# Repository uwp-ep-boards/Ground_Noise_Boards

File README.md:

# Ground_Noise_Boards
Circuit boards to support Ground Noise in Digital Logic lab.

Boards designed by Johnathan Trachte for labs by Dr. Hal Evensen, under guidance by Dr. Cyrus Habibi.

## Revision History
### Signal Board
0.0.2 \
    - Remove grounding from digital logic outputs \
    - Fix LM317LZ silkscreen orientation \
    - Swap LM317LZ programming resistor values to allow minimum current draw under no load \
    - Modify resistor footprint for horizontal mounting \
    - Adjust various power routing as pours instead of tracks \
    - Add test points for critical signals \

### Return Board
0.0.2 \
    - Remove grounding from digital logic outputs \
    - Fix LM317LZ silkscreen orientation \
    - Swap LM317LZ programming resistor values to allow minimum current draw under no load \
    - Modify resistor footprint for horizontal mounting \
    - Add test points for critical signals \

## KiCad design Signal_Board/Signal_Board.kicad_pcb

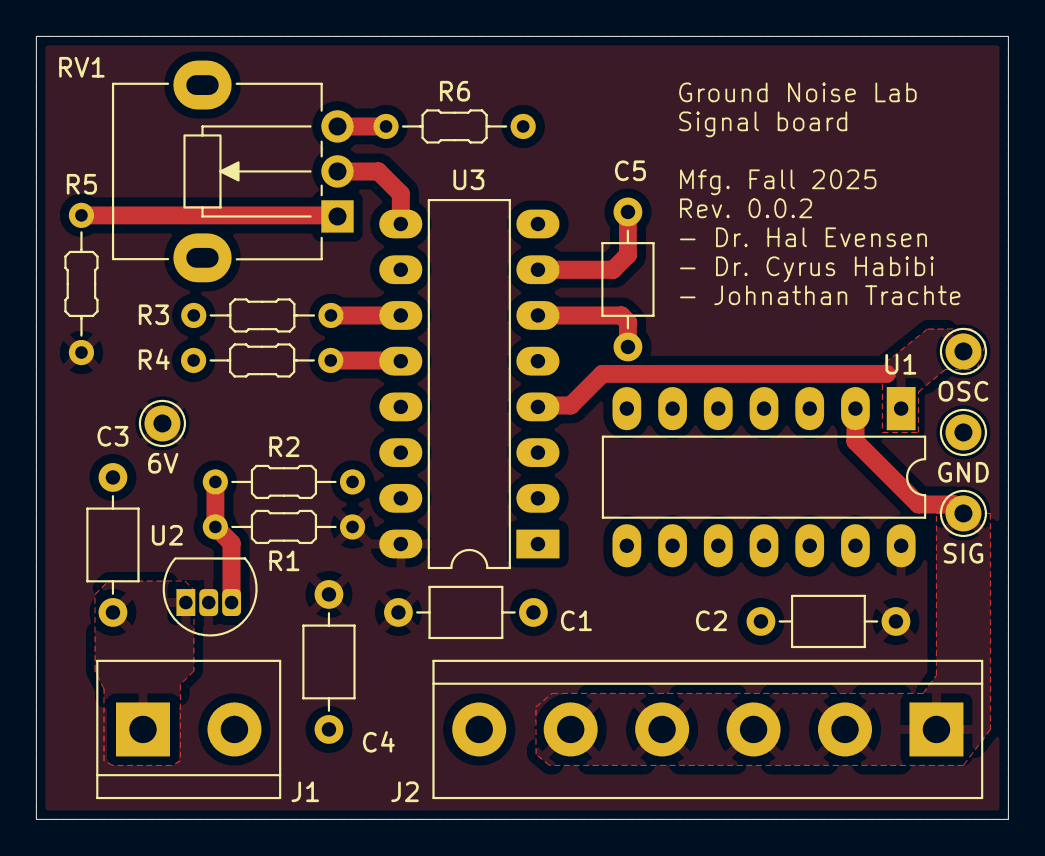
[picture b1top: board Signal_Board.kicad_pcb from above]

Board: 2 copper layers, 54.0 x 43.5 mm, 21 parts (0 on the bottom side), 13 nets.

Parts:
6V: 6 V; Pin_D1.0mm_L10.0mm
C1, C2, C3: 0.1u; C_Axial_L3.8mm_D2.6mm_P7.50mm_Horizontal
C4: 1u; C_Axial_L3.8mm_D2.6mm_P7.50mm_Horizontal
C5: 47p; C_Axial_L3.8mm_D2.6mm_P7.50mm_Horizontal
GND: GND; Pin_D1.0mm_L10.0mm
J1: Conn_01x02_Pin; TerminalBlock_bornier-2_P5.08mm
J2: Conn_01x06_Pin; TerminalBlock_bornier-6_P5.08mm
OSC: Osc; Pin_D1.0mm_L10.0mm
R1: 240; R_Axial_DIN0204_L3.6mm_D1.6mm_P7.62mm_Horizontal
R2: 910; R_Axial_DIN0204_L3.6mm_D1.6mm_P7.62mm_Horizontal
R3: 1k13; R_Axial_DIN0204_L3.6mm_D1.6mm_P7.62mm_Horizontal
R4: 31k6; R_Axial_DIN0204_L3.6mm_D1.6mm_P7.62mm_Horizontal
R5: 1k; R_Axial_DIN0204_L3.6mm_D1.6mm_P7.62mm_Horizontal
R6: 0; R_Axial_DIN0204_L3.6mm_D1.6mm_P7.62mm_Horizontal
RV1: 1M; Potentiometer_Alpha_RD901F-40-00D_Single_Vertical
SIG: Sig; Pin_D1.0mm_L10.0mm
U1: 74HC14; DIP-14_W7.62mm_LongPads
U2: LM317LZ; TO-92L_Inline
U3: 4046; DIP-16_W7.62mm_LongPads

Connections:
+6V: 6V.1, C1.1, C2.1, C4.1, R1.1, R5.1, U1.14 (VCC), U2.3 (OUT), U3.16 (VDD)
+9V: C3.1, J1.1, U2.2 (IN)
/CAP_FB: C5.1, U3.7 (C2)
/LDO_ADJ: R1.2, R2.1, U2.1
/R1: R3.1, U3.11 (R1)
/R2: R4.1, U3.12 (R2)
/SIG_Out: J2.1, J2.2, J2.3, J2.4, J2.5, SIG.1, U1.2
/VCO_IN: RV1.2, U3.9 (VCOin)
GND: C1.2, C2.2, C3.2, C4.2, GND.1, J1.2, J2.6, R2.2, R3.2, R4.2, R6.2, U1.3, U1.5, U1.7 (GND), U1.9, U1.11, U1.13, U3.5 (Inh), U3.8 (VSS), U3.10 (SFout), U3.15 (ZOUT)
unnamed: R5.2, RV1.1
unnamed: R6.1, RV1.3
unnamed: C5.2, U3.6 (C1)
OSC_Out: OSC.1, U1.1, U3.4 (FOUT)

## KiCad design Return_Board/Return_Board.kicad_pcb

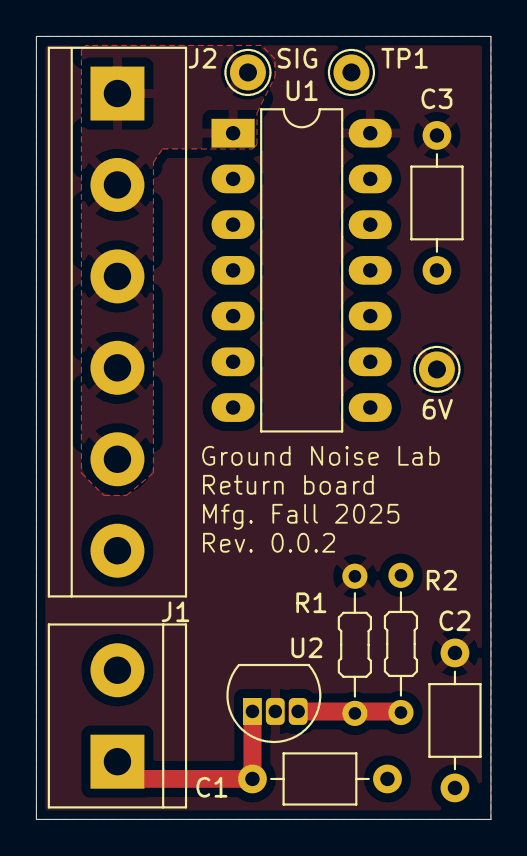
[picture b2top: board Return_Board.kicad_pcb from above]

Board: 2 copper layers, 25.2 x 43.5 mm, 12 parts (0 on the bottom side), 5 nets.

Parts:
6V: 6 V; Pin_D1.0mm_L10.0mm
C1: 0.1u; C_Axial_L3.8mm_D2.6mm_P7.50mm_Horizontal
C2: 1u; C_Axial_L3.8mm_D2.6mm_P7.50mm_Horizontal
C3: C_Small; C_Axial_L3.8mm_D2.6mm_P7.50mm_Horizontal
J1: Conn_01x02_Pin; TerminalBlock_bornier-2_P5.08mm
J2: Conn_01x06_Pin; TerminalBlock_bornier-6_P5.08mm
R1: 240; R_Axial_DIN0204_L3.6mm_D1.6mm_P7.62mm_Horizontal
R2: 910; R_Axial_DIN0204_L3.6mm_D1.6mm_P7.62mm_Horizontal
SIG: SIG; Pin_D1.0mm_L10.0mm
TP1: GND; Pin_D1.0mm_L10.0mm
U1: 74HC14; DIP-14_W7.62mm_LongPads
U2: LM317LZ; TO-92L_Inline

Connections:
+6V: 6V.1, C2.1, C3.1, R1.1, U1.14 (VCC), U2.3 (OUT)
+9V: C1.1, J1.1, U2.2 (IN)
/LDO_ADJ: R1.2, R2.1, U2.1
/SIG_Out: J2.1, J2.2, J2.3, J2.4, J2.5, SIG.1, U1.1
GND: C1.2, C2.2, C3.2, J1.2, J2.6, R2.2, TP1.GND (1), U1.3, U1.5, U1.7 (GND), U1.9, U1.11, U1.13

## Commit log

2025-10-16 test: Verify credentials, update README
2025-11-06 Board version 0.0.1; manufacturing files
2025-12-03 Signal board version 0.0.2; updates in README
2025-12-03 Fix README formatting
2025-12-03 Return board version 0.0.2; updates in README
2025-12-03 Update manufacturing files
